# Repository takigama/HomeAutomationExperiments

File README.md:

# Experiments in Home Automation

So far, there is only the led strip here... there shall be more

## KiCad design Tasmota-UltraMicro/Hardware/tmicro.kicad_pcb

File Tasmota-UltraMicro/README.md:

# The Tasmota Ultra Micro

Like the Tasmota Micro, but smaller.

## Minimal.

I made it so I could put together some small sensor boards that plug straight into
a USB port. Unlike the original Tasmota Micro, this one has only a 'reg and direct
inputs to the GPIO's of the ESP8266 ESP01 board.

## Thanks...

Thanks to the tasmota guys for making the awesome firmware!

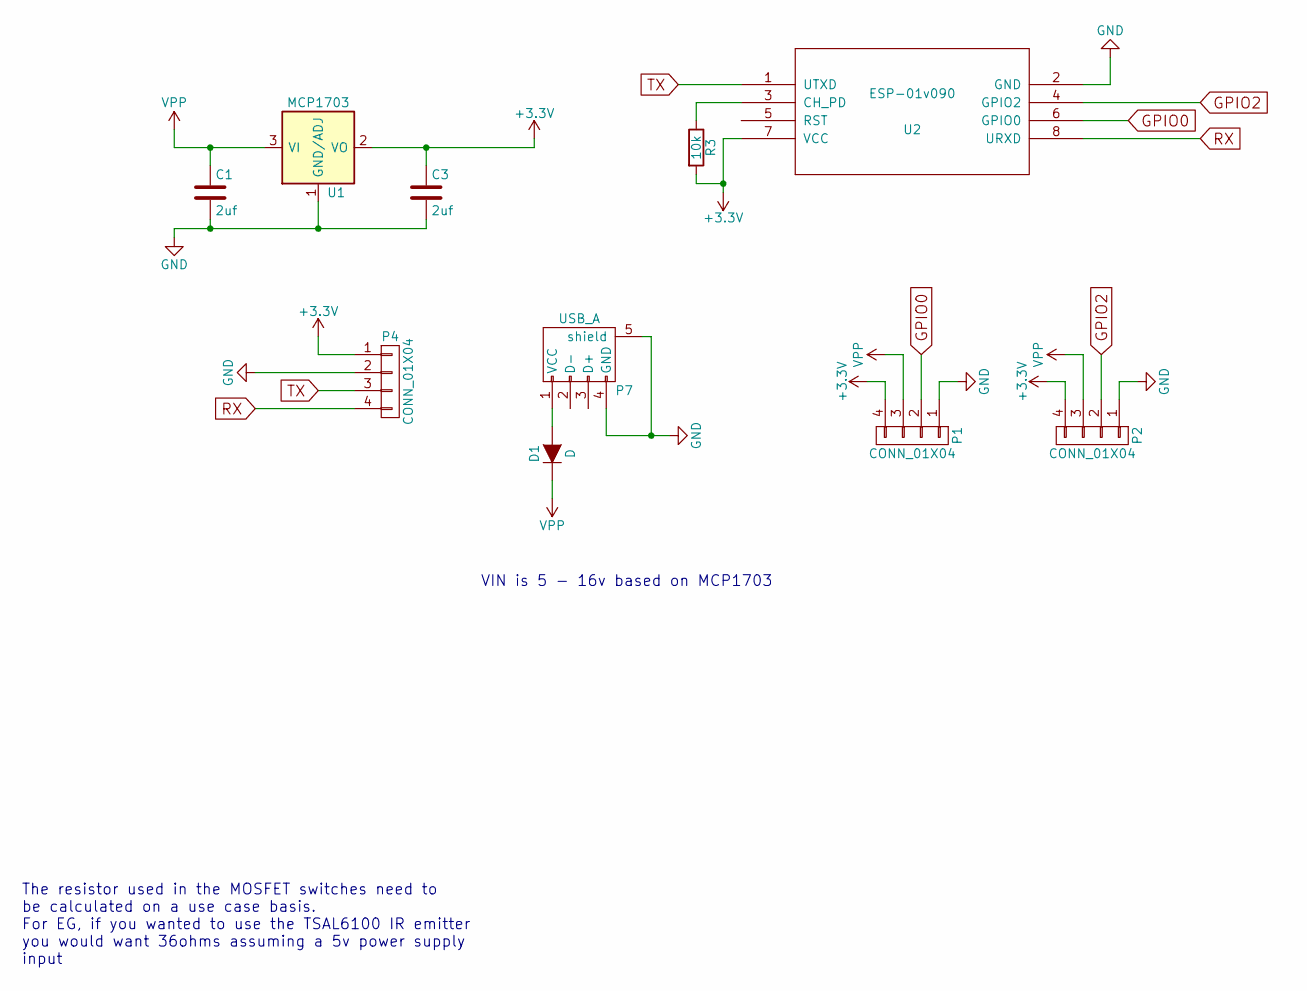
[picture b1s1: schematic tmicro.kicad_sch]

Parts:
C1, C3: 2uf; C_0805
D1: D; SMA_Standard
P1, P2, P4: CONN_01X04; PinHeader_1x04_P2.54mm_Vertical
P7: USB_A; USB_A_Multicomp_thruhole_oshpark
R3: 10k; R_0805
U1: MCP1703; SOT-23
U2: ESP-01v090; ESP-01

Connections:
+3V3: C3.1, P1.4, P2.4, P4.1, R3.2, U1.2 (VO), U2.7 (VCC)
GND: C1.2, C3.2, P1.1, P2.1, P4.2, P7.4 (GND), P7.5 (shield), U1.1 (GND/ADJ), U2.2 (GND)
GPIO0: P1.2, U2.6 (GPIO0)
GPIO2: P2.2, U2.4 (GPIO2)
unnamed: D1.2 (A), P7.1 (VCC)
unnamed: R3.1, U2.3 (CH_PD)
RX: P4.4, U2.8 (URXD)
TX: P4.3, U2.1 (UTXD)
VPP: C1.1, D1.1 (K), P1.3, P2.3, U1.3 (VI)

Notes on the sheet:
VIN is 5 - 16v based on MCP1703
The resistor used in the MOSFET switches need to be calculated on a use case basis. For EG, if you wanted to use the TSAL6100 IR emitter you would want 36ohms assuming a 5v power supply input

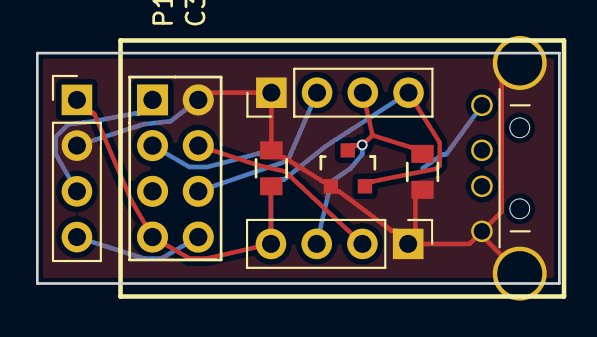
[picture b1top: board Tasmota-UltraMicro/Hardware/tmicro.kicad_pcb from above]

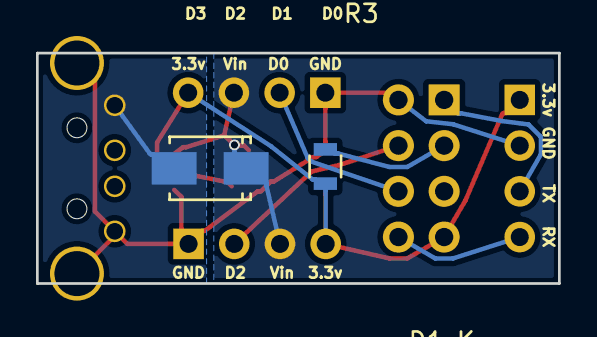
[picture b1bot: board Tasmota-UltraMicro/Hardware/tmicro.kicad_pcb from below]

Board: 2 copper layers, 29.0 x 12.8 mm, 10 parts (2 on the bottom side), 9 nets.

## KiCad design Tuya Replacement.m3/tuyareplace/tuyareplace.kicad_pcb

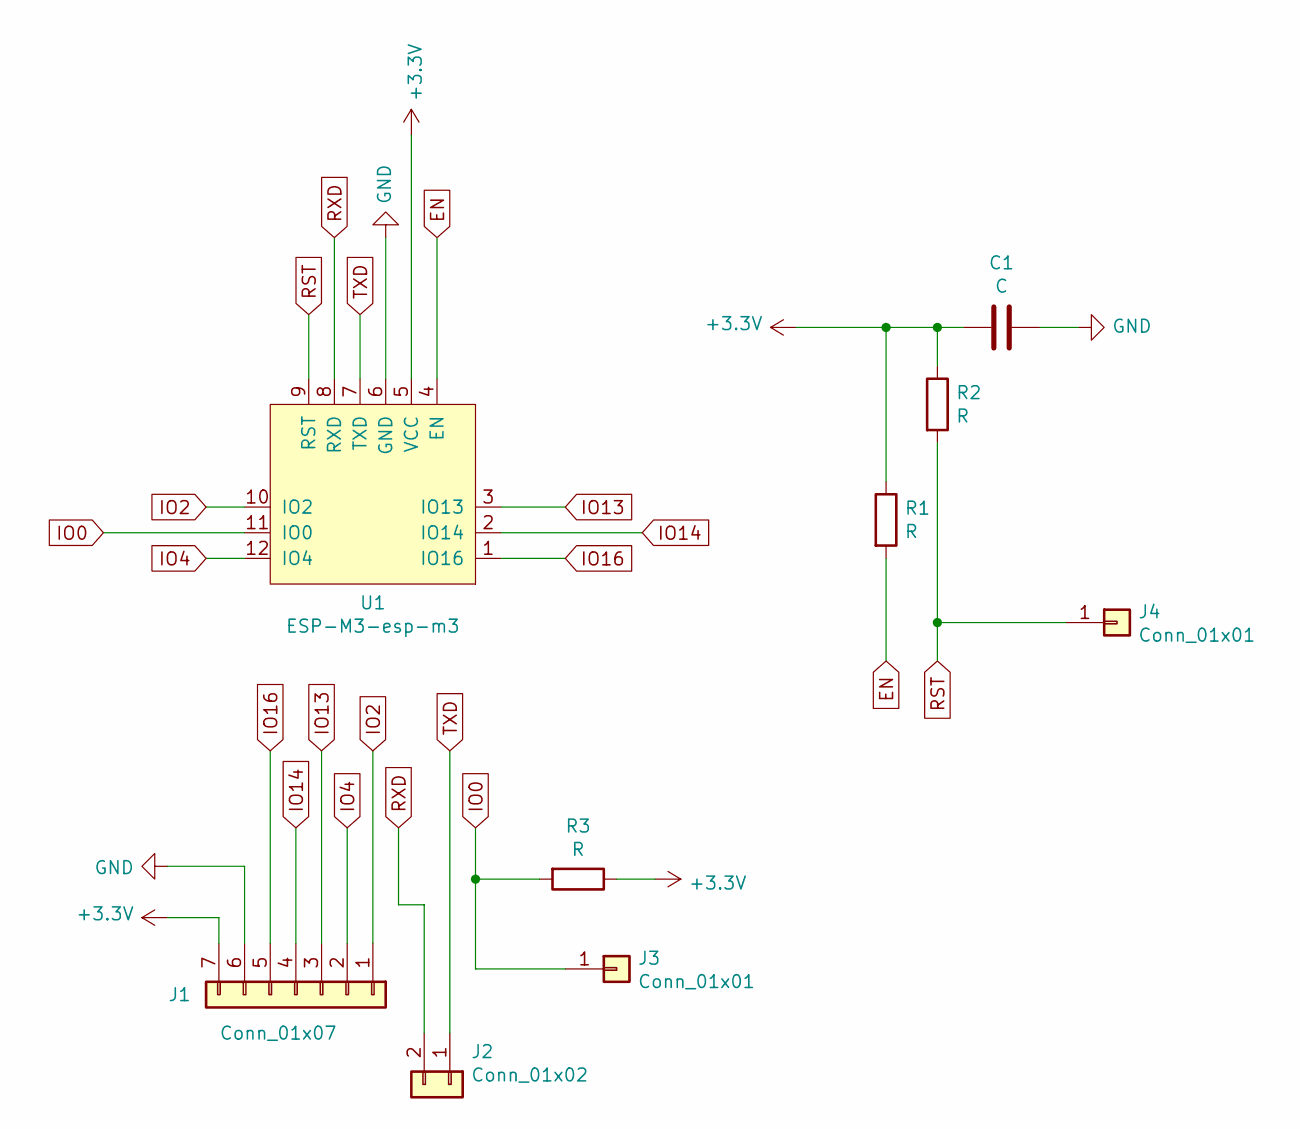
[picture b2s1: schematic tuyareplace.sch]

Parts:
C1: C; C_1206_3216Metric
J1: Conn_01x07; Tuya_TYWE2L_Edge
J2: Conn_01x02; PinHeader_1x02_P2.54mm_Vertical
J3, J4: Conn_01x01; PinHeader_1x01_P2.54mm_Vertical
R1, R2, R3: R; R_1206_3216Metric
U1: ESP-M3-esp-m3; ESP-M3

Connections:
+3V3: C1.2, J1.7, R1.1, R2.1, R3.1, U1.5 (VCC)
EN: R1.2, U1.4 (EN)
GND: C1.1, J1.6, U1.6 (GND)
IO0: J3.1, R3.2, U1.11 (IO0)
IO2: J1.1, U1.10 (IO2)
IO4: J1.2, U1.12 (IO4)
IO13: J1.3, U1.3 (IO13)
IO14: J1.4, U1.2 (IO14)
IO16: J1.5, U1.1 (IO16)
RST: J4.1, R2.2, U1.9 (RST)
RXD: J2.2, U1.8 (RXD)
TXD: J2.1, U1.7 (TXD)

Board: 2 copper layers, 9 parts (8 on the bottom side), 12 nets, no tracks yet.

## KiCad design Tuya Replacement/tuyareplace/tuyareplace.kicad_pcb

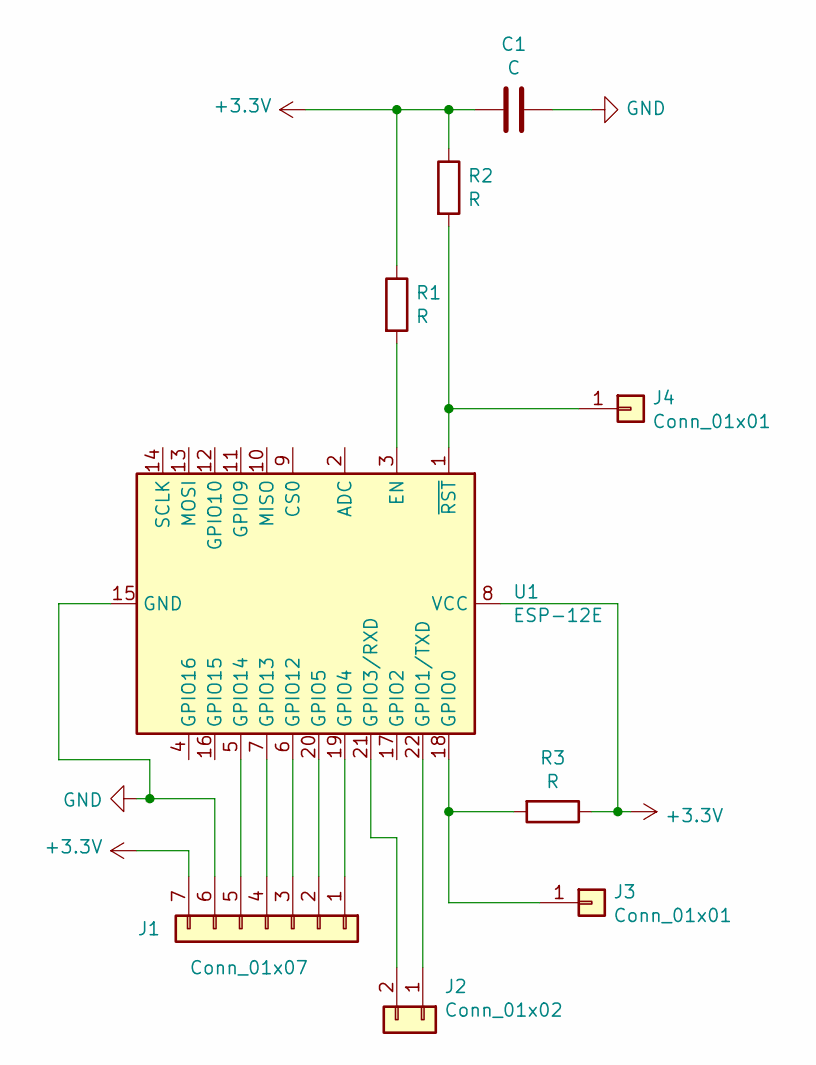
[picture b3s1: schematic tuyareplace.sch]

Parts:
C1: C; C_1206_3216Metric
J1: Conn_01x07; Tuya_TYWE2L_Edge
J2: Conn_01x02; PinHeader_1x02_P2.54mm_Vertical
J3, J4: Conn_01x01; PinHeader_1x01_P2.54mm_Vertical
R1, R2, R3: R; R_1206_3216Metric
U1: ESP-12E

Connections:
+3V3: C1.2, J1.7, R1.1, R2.1, R3.1, U1.8 (VCC)
GND: C1.1, J1.6, U1.15 (GND)
unnamed: J1.1, U1.19 (GPIO4)
unnamed: J1.2, U1.20 (GPIO5)
unnamed: J1.3, U1.6 (GPIO12)
unnamed: J1.4, U1.7 (GPIO13)
unnamed: J1.5, U1.5 (GPIO14)
unnamed: J2.1, U1.22 (GPIO1/TXD)
unnamed: J2.2, U1.21 (GPIO3/RXD)
unnamed: J3.1, R3.2, U1.18 (GPIO0)
unnamed: J4.1, R2.2, U1.1 (~RST)
unnamed: R1.2, U1.3 (EN)

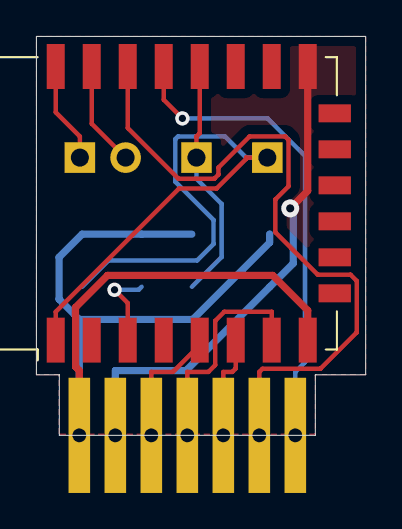
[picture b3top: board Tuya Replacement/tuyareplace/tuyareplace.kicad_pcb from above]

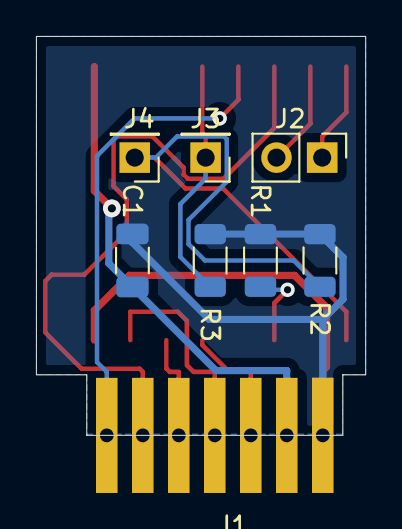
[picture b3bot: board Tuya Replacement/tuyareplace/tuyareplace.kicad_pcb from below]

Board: 2 copper layers, 18.3 x 22.2 mm, 9 parts (8 on the bottom side), 12 nets.

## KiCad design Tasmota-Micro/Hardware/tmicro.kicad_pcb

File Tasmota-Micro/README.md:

# The Tasmota Micro board

The tasmota micro (hope they dont mine me calling it that) is based off my
ledstrip controller with alot more flexibility build it. Its quite straight
forward but i'll make an image shortly of where the components go on the
board.

In short, the BOM is:

1. 2 x IRLML6244 (if needed - provides switching output for higher current
   loads) - Q1 and Q2
2. 2 x 2.2uf (or higher), one rated for 3.6v min and the othr rated at
   whatever input voltage you use. C3 - 3.3v, C1 Input voltage
3. 1 x diode (for stopping reverse polarity on the input) - D1
4. MCP1703-3.3 (3.3v regulator rated at 250ma - just enough for this) U1
5. 2 x resistors (you must size these yourself - but notes are provided) R1/2
6. 1 x 20k resistor - R3
7. 1 x MC32603 USB connector (only needed if you wish to poer the thing
   in the way i've show in my pictures, it can be just wired in.
8. Optionally a 2x4 header strip.
9. And of course, you will want an ESP-01S (with the larger flash, though I
   believe it can work ith the smaller 512k flash if you cut the firmware
   down a bit).

All resistors and caps are 0805 size. Diode is SMA.

## Putting it together

Personally, my first one was a hand solder job with a nothing-special type
of soldering iron and I found this to be quite easy (though I used a handheld
magnifying glass to get the components lined up). I put the first one together
with these tools just to make sure it could be done easily enough.

Generally I would normally use solder paste and a heatgun for the SMD
components, then hand solder in the connectors. Also note, in the images, i've
put JST connectors on there, this is just a serving suggestion, its not a
requirement and I wouldn't recommend it.

Also note, for the ESP module in the images, i've put on a 4x2 header so I
can easily remove the ESP-01 module - this isnt a requirement as it makes
the module quite a bit shorter if you choose not to do this. The ESP can still
be flashed if needed while soldered to the board, but you'll need some small
clips to do it.

## Connectors

### P2

Proves both raw input voltage or raw output voltage - i.e. you can push
power into the unit via one of these pins or provide power at the input
voltage as output (i.e. if your driving from USB these pins are 5v). Maximum
input voltate is 16v according to the MCP1703 tech specs, but I wouldn't
have a need to go beyond 12v myself.

### P3

These are the mosfet switched versions of GPIO2 and the RX line. They also
include current limiting resistors, R1 and R2 - you must size these
appropriaely for your project (or just bridge them and put resistors on
your actual device). Note, these pull to ground!

### P4

This header provides all 4 GPIO's as direct connections on the ESP at the
level of the ESP itself (3.3v), be aware though that depending on the state
of the ESP itself (which can draw about 170ma max - apparently), you can only
draw a maxmimum of about 80ma!.

### P5 

Output from the MCP1703 regulator is provided on these pins. This would
typically be 3.3v but if you've put in your own changes, what comes out
there is up to you, i.e. configure that in the tasmota gui.

### P6

Ground pins

## GPIO's

The device provides 4 GPIO's as well as two that can be switched via
mosfets.

So far i've tested the following components:

1. HC-SR505 movement sensor
2. BME280 - Temp/Pressure/Humidity
3. BMP180 - Temp/Pressure
4. BH1750 - Ambient light
5. CHQ1838 - IR Recv (runs at 3.3v, work well)
6. DS18B20 - Dallas Temp Sensor
7. TSAL6100 - IR Emitter (47ohm resistor on mosfet switch).
8. WS2812 - Addressable led strip.

So far they all work well - keen to try some more if and when i can think of
something.

## Current Limiting Resistors

On the "high current" switches (which are RX and GPIO2 on P3) you must either
provide some current limiting resistors or bridge the resistor tracks and put
the resistors on your device (assuming you need them at all). This also means
they must be sized to suit your needs (if putting them on the board). As an
example, I have one with a 47ohm resistor (to drive the TSAL6000 IR emitter)
and one with a 150ohm resistor (cause why not?).

Also note the mosfet i've put in the bom on this are rated for 6a, however I
wouldn't push my luck with it as the tracks can probably only withstand about
2A depending on the thickness of the solder traces and where you get them made.
Personally, I use OSH Park (note the connector the USB is designed with
circular holes for the USB mount ends - this is because OSH Park dont do oval
drill holes).

## More to come

As I get the opportunity i'll test some other devices to hang off it and will
definitely be continuing to update the board as time permits.

## Thanks...

Thanks to the tasmota guys for making the awesome firmware!

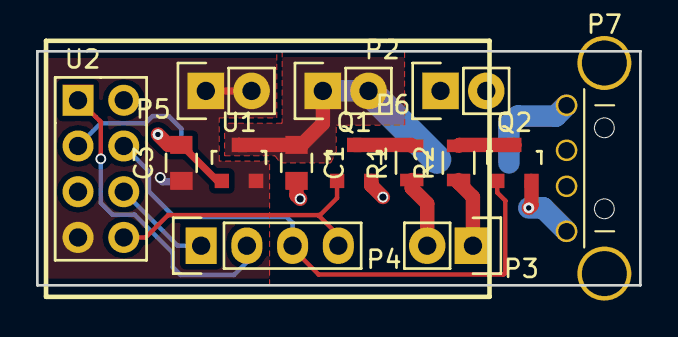
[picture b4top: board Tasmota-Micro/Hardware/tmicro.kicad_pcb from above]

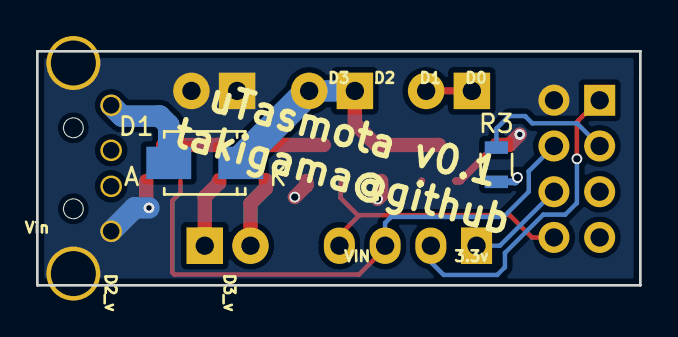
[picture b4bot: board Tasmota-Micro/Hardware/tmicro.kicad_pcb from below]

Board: 2 copper layers, 33.5 x 13.0 mm, 16 parts (2 on the bottom side), 13 nets.

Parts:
C1, C3: 2uf; C_0805
D1: D; SMA_Standard
P2, P3, P5, P6: CONN_01X02; Pin_Header_Straight_1x02
P4: CONN_01X04; Pin_Header_Straight_1x04
P7: USB_A; USB_A_Multicomp_thruhole_oshpark
Q1, Q2: IRLML6244; SOT-23
R1, R2: X; R_0805
R3: 10k; R_0805
U1: MCP1703; SOT-23
U2: ESP-01v090; ESP-01

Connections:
+3V3: C3.1, P5.1, P5.2, R3.2, U1.2, U2.7
GND: C1.2, C3.2, P6.1, P6.2, P7.4, P7.5, Q1.2, Q2.2, U1.1, U2.2
GPIO0: P4.1, U2.6
GPIO2: P4.3, Q2.1, U2.4
GPIO2_V: P3.1, R2.2
unnamed: D1.2, P7.1
unnamed: Q1.3, R1.1
unnamed: Q2.3, R2.1
unnamed: R3.1, U2.3
RX: P4.4, Q1.1, U2.8
RX_V: P3.2, R1.2
TX: P4.2, U2.1
VPP: C1.1, D1.1, P2.1, P2.2, U1.3

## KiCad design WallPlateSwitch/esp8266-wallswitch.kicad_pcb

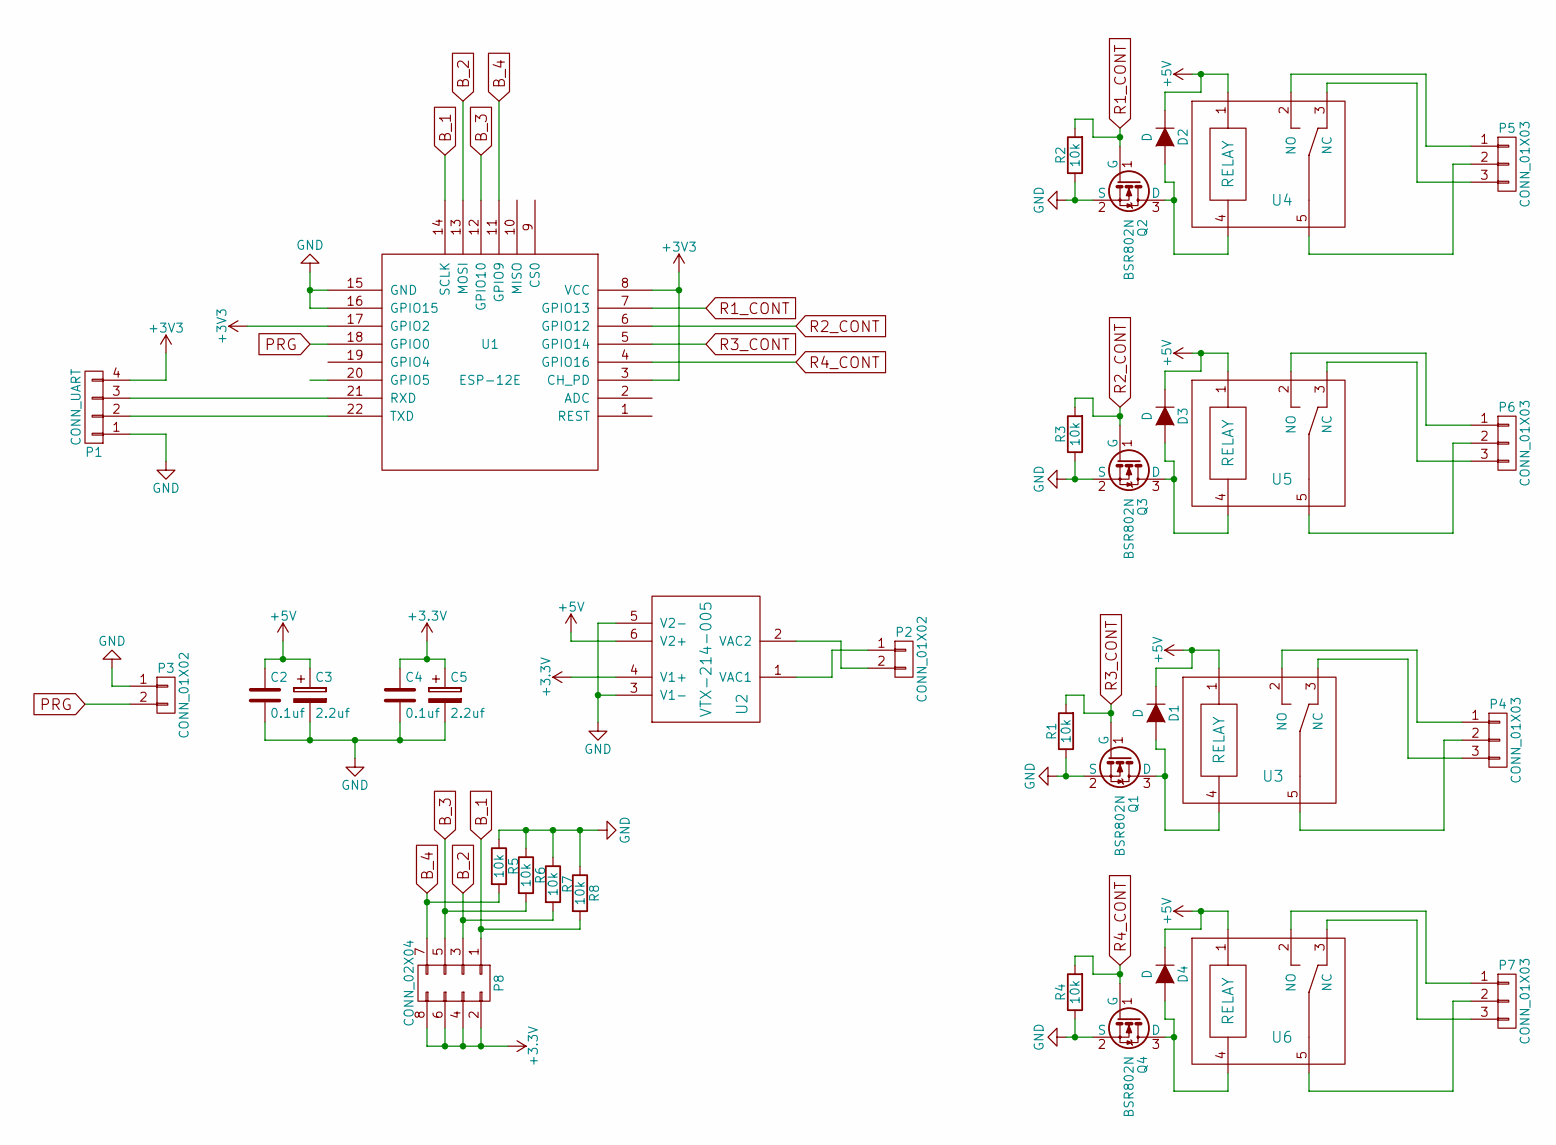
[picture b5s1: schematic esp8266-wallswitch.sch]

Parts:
C2, C4: 0.1uf; C_0805_HandSoldering
C3, C5: 2.2uf; SMD-1210_Pol
D1, D2, D3, D4: D; SMA_Standard
P1: CONN_UART; Pin_Header_Straight_1x04
P2: CONN_01X02; TerminalBlock_Pheonix_MKDS1.5-2pol
P3: CONN_01X02; Pin_Header_Straight_1x02
P4, P5, P6, P7: CONN_01X03; TerminalBlock_Pheonix_MKDS1.5-3pol
P8: CONN_02X04; Pin_Header_Straight_2x04
Q1, Q2, Q3, Q4: BSR802N; SOT-23_Handsoldering
R1, R2, R3, R4, R5, R6, R7, R8: 10k; R_0805_HandSoldering
U1: ESP-12E; ESP-12E-nohole
U2: VTX-214-005
U3, U4, U5, U6: RELAY; SONGLE_RELAY

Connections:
+5V: C2.1, C3.1, D1.1 (K), D2.1 (K), D3.1 (K), D4.1 (K), U2.6 (V2+), U3.1, U4.1, U5.1, U6.1
B_1: P8.1, R8.2, U1.14 (SCLK)
B_2: P8.3, R7.2, U1.13 (MOSI)
B_3: P8.5, R6.2, U1.12 (GPIO10)
B_4: P8.7, R5.2, U1.11 (GPIO9)
GND: C2.2, C3.2, C4.2, C5.2, P1.1, P3.1, Q1.2 (S), Q2.2 (S), Q3.2 (S), Q4.2 (S), R1.1, R2.1, R3.1, R4.1, R5.1, R6.1, R7.1, R8.1, U1.15 (GND), U1.16 (GPIO15), U2.3 (V1-), U2.5 (V2-)
unnamed: D1.2 (A), Q1.3 (D), U3.4
unnamed: D2.2 (A), Q2.3 (D), U4.4
unnamed: D3.2 (A), Q3.3 (D), U5.4
unnamed: D4.2 (A), Q4.3 (D), U6.4
unnamed: P1.2, U1.22 (TXD)
unnamed: P1.3, U1.21 (RXD)
unnamed: P2.1, U2.1 (VAC1)
unnamed: P2.2, U2.2 (VAC2)
unnamed: P4.1, U3.2 (NO)
unnamed: P4.2, U3.5
unnamed: P4.3, U3.3 (NC)
unnamed: P5.1, U4.2 (NO)
unnamed: P5.2, U4.5
unnamed: P5.3, U4.3 (NC)
unnamed: P6.1, U5.2 (NO)
unnamed: P6.2, U5.5
unnamed: P6.3, U5.3 (NC)
unnamed: P7.1, U6.2 (NO)
unnamed: P7.2, U6.5
unnamed: P7.3, U6.3 (NC)
PRG: P3.2, U1.18 (GPIO0)
R1_CONT: Q2.1 (G), R2.2, U1.7 (GPIO13)
R2_CONT: Q3.1 (G), R3.2, U1.6 (GPIO12)
R3_CONT: Q1.1 (G), R1.2, U1.5 (GPIO14)
R4_CONT: Q4.1 (G), R4.2, U1.4 (GPIO16)

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
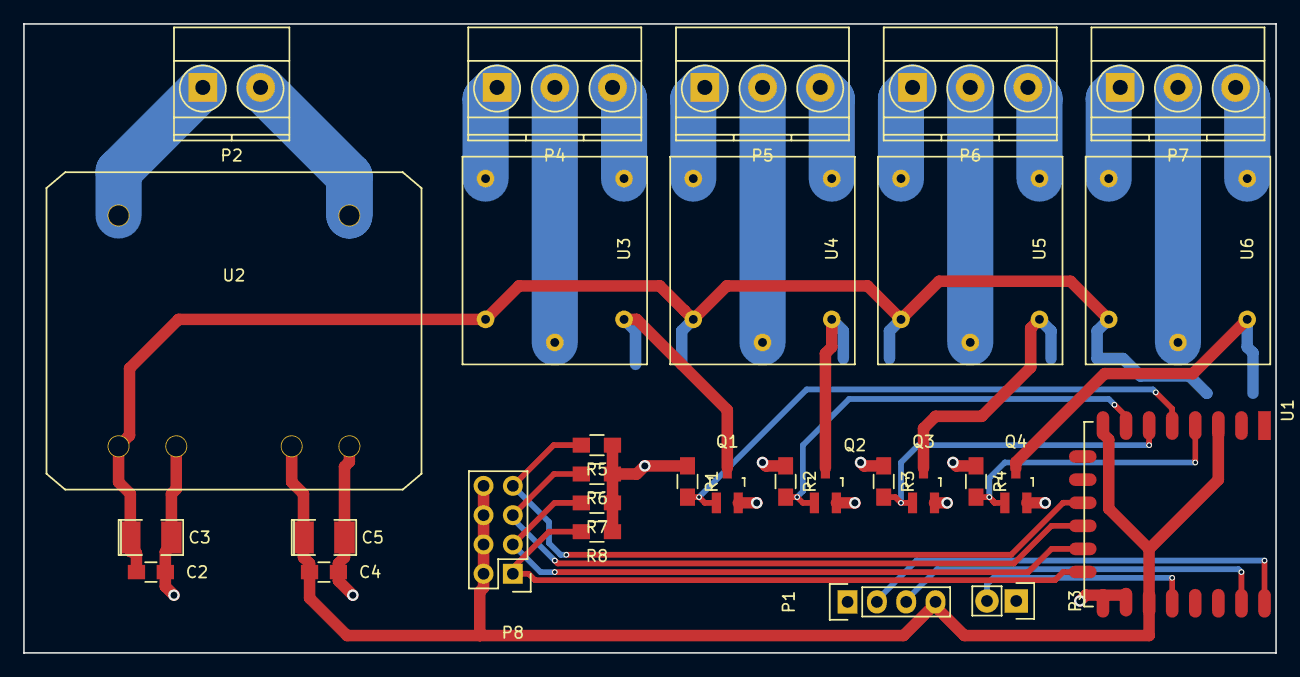
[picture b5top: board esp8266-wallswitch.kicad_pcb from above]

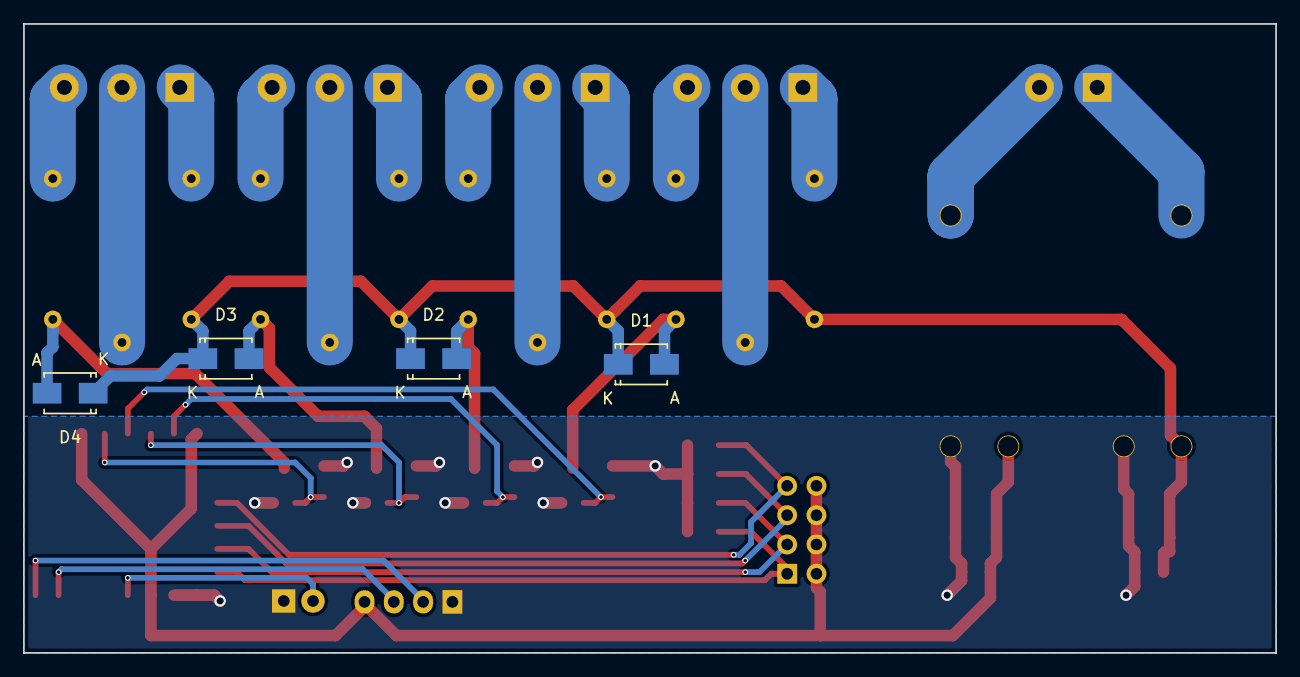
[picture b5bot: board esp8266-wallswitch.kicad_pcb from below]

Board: 2 copper layers, 108.5 x 54.5 mm, 34 parts (4 on the bottom side), 32 nets.

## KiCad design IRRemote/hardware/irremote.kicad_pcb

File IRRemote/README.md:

# ESP8266 based IR remote

This project is an ESP8266/homie based IR remote receiver/transmitter
The board uses a ESP12E as its base. There are several parts that can
be left off if not needed. For EG, it uses 4 transistors, one for each
of 4 IR leds, each can handle about 500ma of output at 5v, which means
all 4 together give about 2a across 4 connectors so size appropriately

The board has a connections for a TEMT6000 Light sensor as well as the
DS18B20 single wire temperature chip. All the spare GPIO's are exposed
as well as the SPI interface to be used for whatever you like. The ADC
pin of the ESP is connected to the light sensor, so if you want to use
it for a different purpose, you can connect it there.

## Homie + ESP8266

This board was designed with homie in mind and uses MQTT to comm's
with its controller. In my case, Home Assistant. As this hasnt been
written yet, i'll get back to you shortly!

## Image

## Warning!

Only just got the board back from OSHPark, but so far it works ok. I've
managed to control a device via IR after learning its IR message via
the ESP8266 IR library. Fairly happy so far. Temperature is also working
quite well. Only issue i have with it is that the SMD push button 
footprint I used is slightly smaller then the actual PB's I have, which
made soldering them on quite the pain.

## Changes

* moved to a microusb connector for power
* flipped the IR receiver so its pointing outward
* fixed the push buttons for the correct SMD push button

OshPark Project: [Link](https://oshpark.com/shared_projects/F54xaFnq)

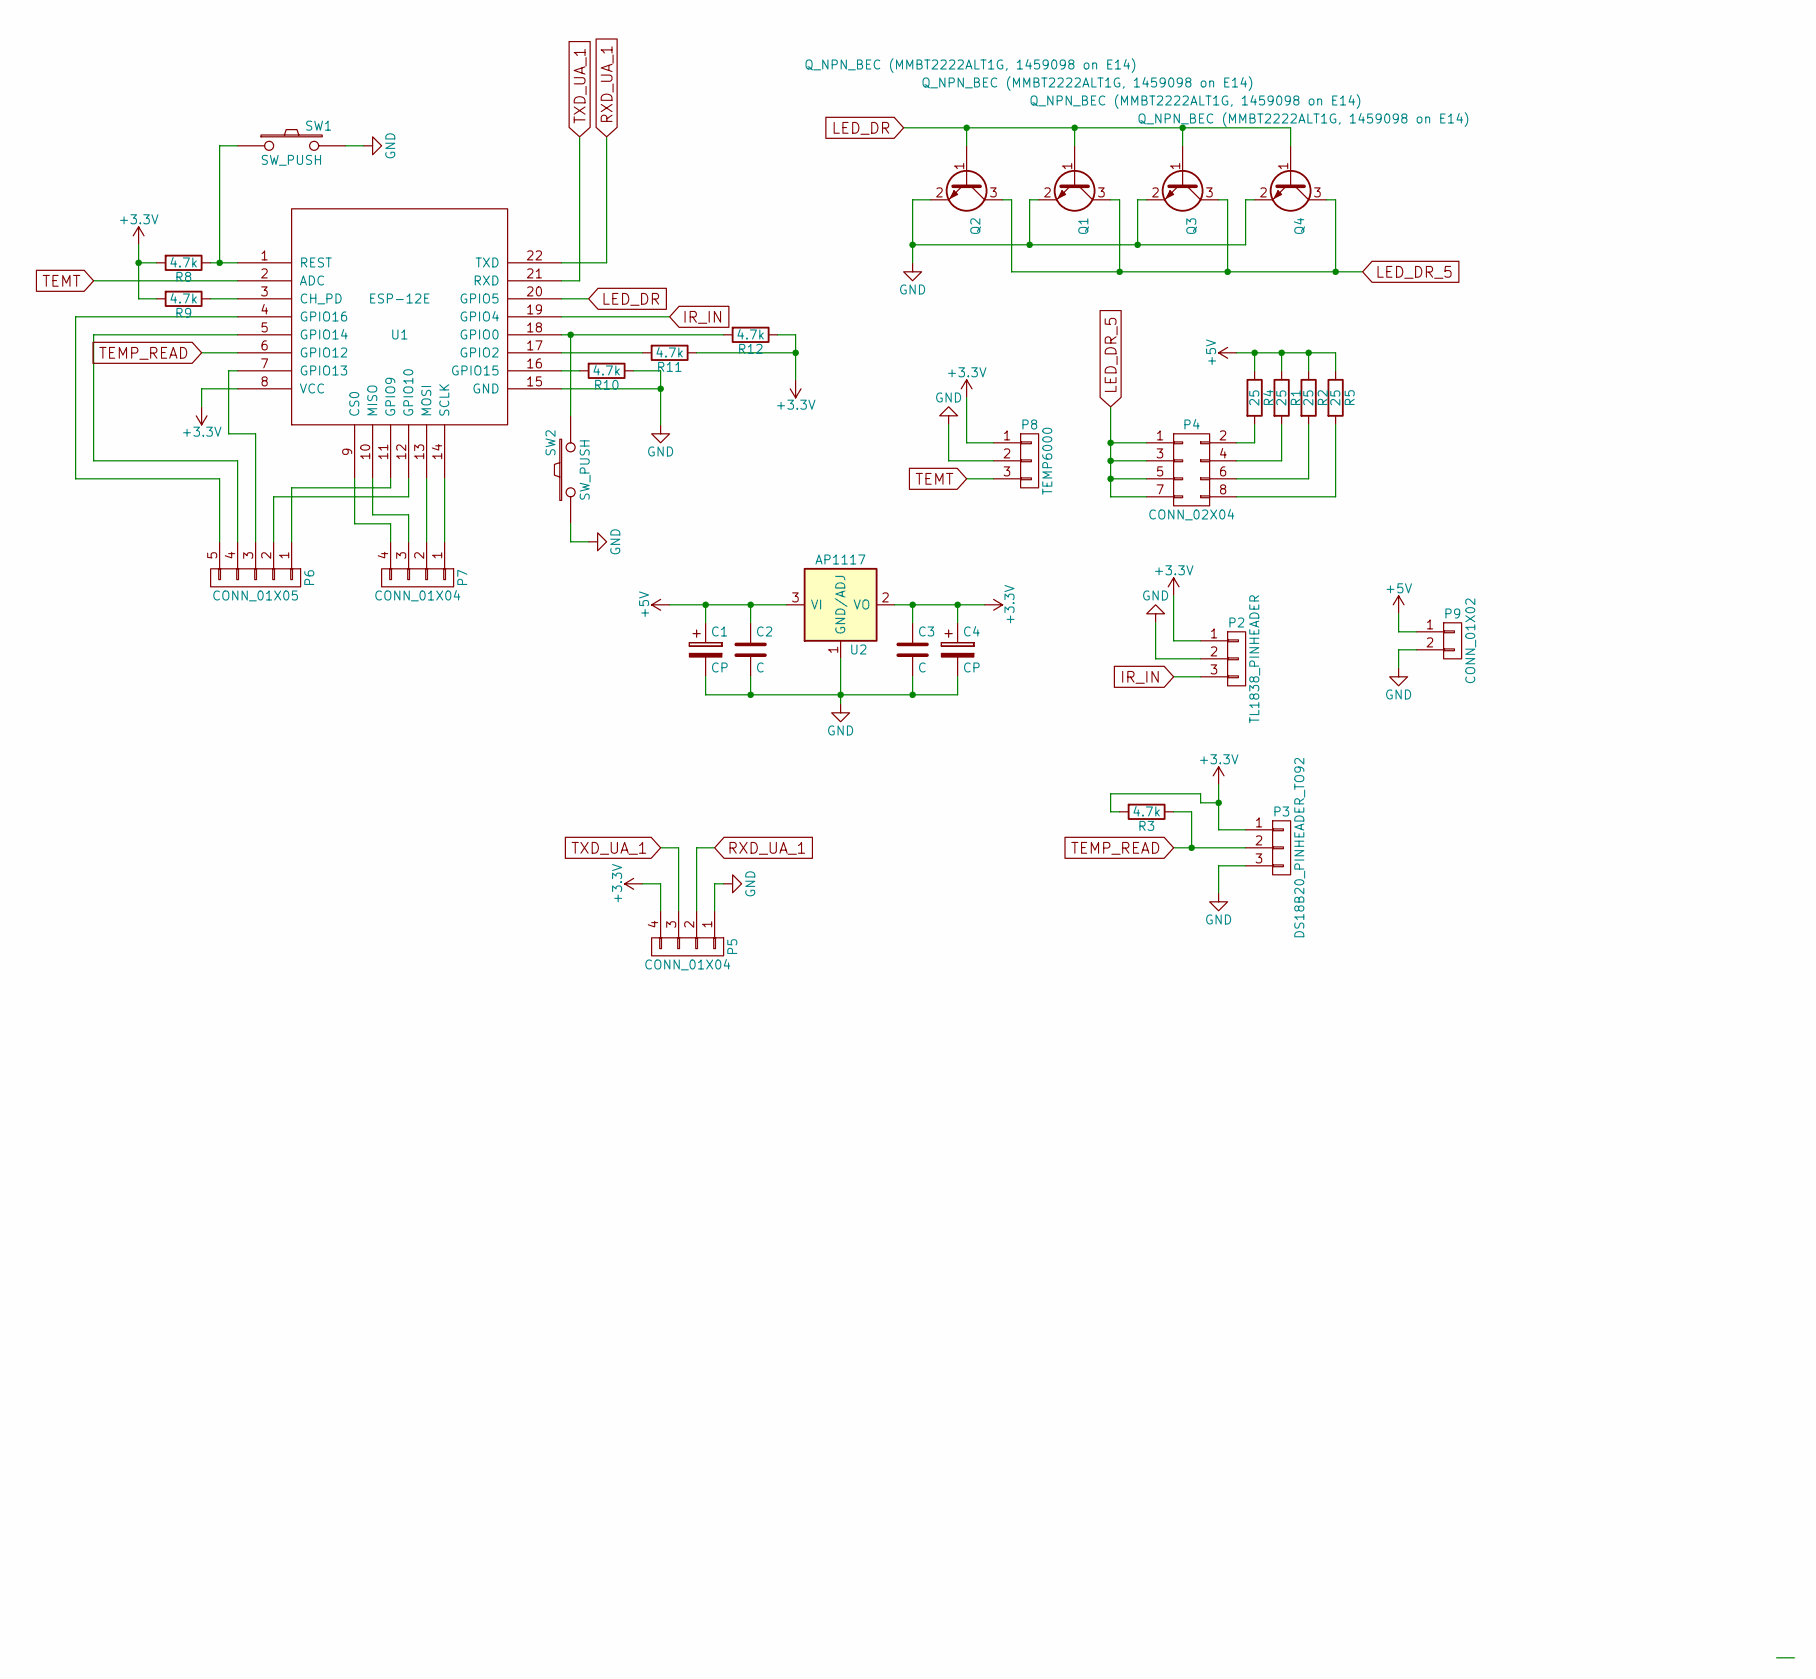
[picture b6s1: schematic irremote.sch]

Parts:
C1, C4: CP; TantalC_SizeB_EIA-3528_Reflow
C2, C3: C; C_0805
P2: TL1838_PINHEADER; Pin_Header_Straight_1x03
P3: DS18B20_PINHEADER_TO92; TO-92_Inline_Narrow_Oval
P4: CONN_02X04; Pin_Header_Straight_2x04
P5, P7: CONN_01X04; Pin_Header_Straight_1x04
P6: CONN_01X05; Pin_Header_Straight_1x05
P8: TEMP6000; Pin_Header_Straight_1x03
P9: CONN_01X02; Pin_Header_Straight_1x02
Q1, Q2, Q3, Q4: Q_NPN_BEC (MMBT2222ALT1G, 1459098 on E14); SOT-23
R1, R2, R4, R5: 25; R_0805_HandSoldering
R3, R8, R9, R10, R11, R12: 4.7k; R_0805_HandSoldering
SW1, SW2: SW_PUSH; SW_SPST_FSMSM
U1: ESP-12E
U2: AP1117; SOT-23_Handsoldering

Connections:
+3V3: C3.1, C4.1, P2.1, P3.1, P5.4, P8.1, R3.2, R8.2, R9.2, R11.1, R12.1, U1.8 (VCC), U2.2 (VO)
+5V: C1.1, C2.1, P9.1, R1.1, R2.1, R4.1, R5.1, U2.3 (VI); also elsewhere on the board
GND: C1.2, C2.2, C3.2, C4.2, P2.2, P3.3, P5.1, P8.2, P9.2, Q1.2 (E), Q2.2 (E), Q3.2 (E), Q4.2 (E), R10.1, SW1.2, SW2.1, U1.15 (GND), U2.1 (GND/ADJ); also elsewhere on the board
IR_IN: P2.3, U1.19 (GPIO4)
LED_DR: Q1.1 (B), Q2.1 (B), Q3.1 (B), Q4.1 (B), U1.20 (GPIO5)
LED_DR_5: P4.1, P4.3, P4.5, P4.7, Q1.3 (C), Q2.3 (C), Q3.3 (C), Q4.3 (C)
unnamed: P4.2, R4.2
unnamed: P4.4, R1.2
unnamed: P4.6, R2.2
unnamed: P4.8, R5.2
unnamed: P6.1, U1.11 (GPIO9)
unnamed: P6.2, U1.12 (GPIO10)
unnamed: P6.3, U1.7 (GPIO13)
unnamed: P6.4, U1.5 (GPIO14)
unnamed: P6.5, U1.4 (GPIO16)
unnamed: P7.1, U1.14 (SCLK)
unnamed: P7.2, U1.13 (MOSI)
unnamed: P7.3, U1.10 (MISO)
unnamed: P7.4, U1.9 (CS0)
unnamed: R8.1, SW1.1, U1.1 (REST)
unnamed: R9.1, U1.3 (CH_PD)
unnamed: R10.2, U1.16 (GPIO15)
unnamed: R11.2, U1.17 (GPIO2)
unnamed: R12.2, SW2.2, U1.18 (GPIO0)
RXD_UA_1: P5.2, U1.22 (TXD)
TEMP_READ: P3.2, R3.1, U1.6 (GPIO12)
TEMT: P8.3, U1.2 (ADC)
TXD_UA_1: P5.3, U1.21 (RXD)

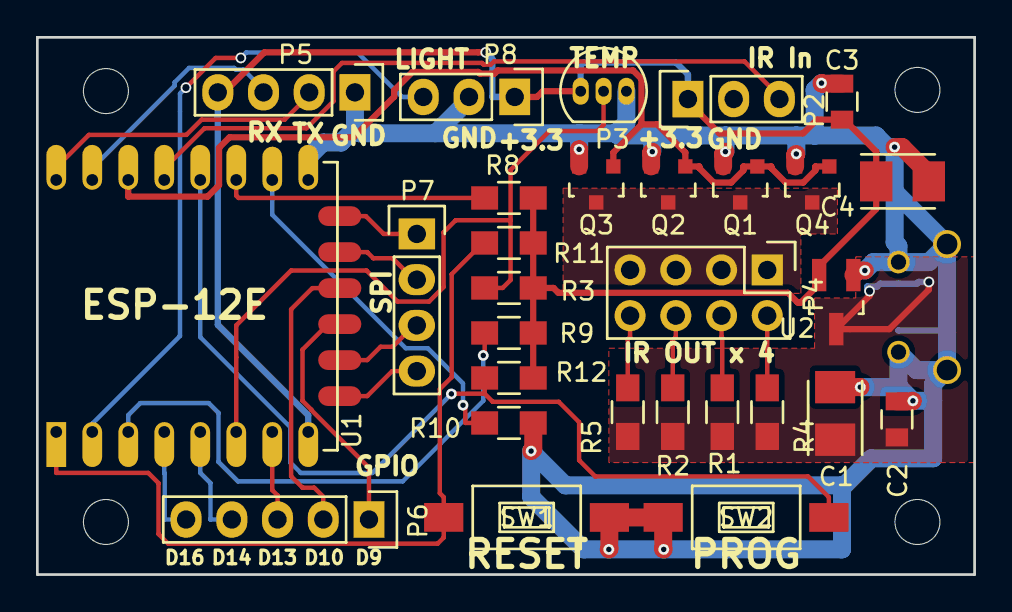
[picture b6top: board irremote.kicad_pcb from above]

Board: 2 copper layers, 52.1 x 29.8 mm, 34 parts (1 on the bottom side), 28 nets.

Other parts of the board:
P1: USB_OTG; USB_Micro-B-OshPark
REF01, REF02, REF03, REF04: MountingHole_2-5mm

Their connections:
+5V: P1.1; also elsewhere on the board
GND: P1.5, P1.6; also elsewhere on the board

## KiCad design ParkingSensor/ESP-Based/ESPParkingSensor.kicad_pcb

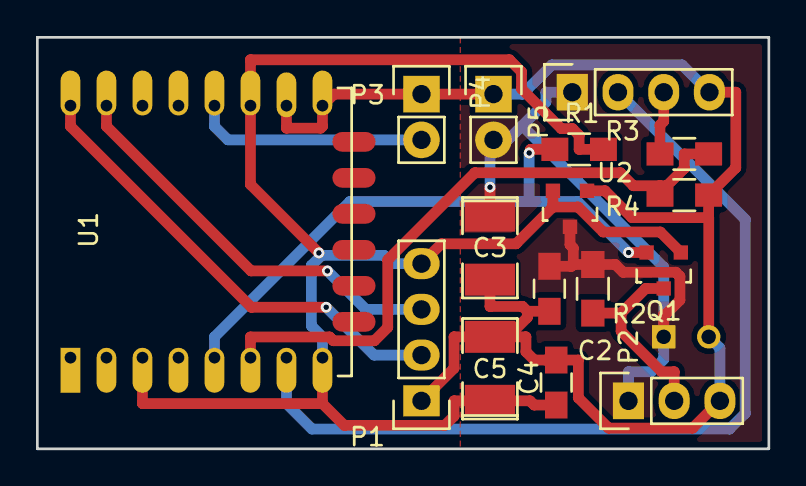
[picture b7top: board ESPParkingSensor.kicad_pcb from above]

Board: 2 copper layers, 40.6 x 22.9 mm, 17 parts (1 on the bottom side), 11 nets.

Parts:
C1: 1000uf; C_Radial_D6.3_L11.2_P2.5
C2, C4: 0.1uf; C_0805_HandSoldering
C3, C5: 2.2uf; SMD-1210_Pol
P1: CONN_UART; Pin_Header_Straight_1x04
P2: CONN_WS2812; Pin_Header_Straight_1x03
P3, P5: CONN_01X02; Pin_Header_Straight_1x02
P4: CONN_US; Pin_Header_Straight_1x04
Q1: BSS138; SOT-23
R1, R2: 10k; R_0805_HandSoldering
R3: 1.7k; R_0805_HandSoldering
R4: 3.3k; R_0805_HandSoldering
U1: ESP-12E
U2: MCP1700; SOT-23

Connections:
+3V3: C4.1, C5.1, P1.4, Q1.1, R1.1, U1.3, U1.8, U1.17, U2.2
+5V: C1.1, C2.1, C3.1, P2.1, P4.1, P5.2, R2.1, U2.3
BB_LINE: Q1.2, R1.2, U1.5
BB_LINE_5: P2.2, Q1.3, R2.2
ECHO: P4.3, R3.1
GND: C1.2, C2.2, C3.2, C4.2, C5.2, P1.1, P2.3, P3.1, P4.4, P5.1, R4.2, U1.15, U1.16, U2.1
unnamed: P1.2, U1.22
unnamed: P1.3, U1.21
unnamed: R3.2, R4.1, U1.6
PRG: P3.2, U1.18
TRG: P4.2, U1.7

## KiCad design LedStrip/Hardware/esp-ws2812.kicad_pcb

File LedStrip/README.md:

# Dont build this....

Im currently in the process of re-designing this board based on the tasmota
firmware so I would hold off building one of these boards in favour of my new
uTasmota board - very similar size, and more flexible.

If you really do want to build this board, go ahead, but rather than using
my own homie-based firmware, flash the tasmota firmware (make sure you using
a board that has 1mb of flash, not 512k).

.... continueing on...

# Led strip for ESP8266 with homie and hardware

This is a little code base and a hardware board designed to work with homie
and the WS2812 led strips. The hardware component is based on the ESP-01, that
is you print the board, put its components on, then add an ESP-01 (or s).

* [OSHPark Project](https://oshpark.com/shared_projects/sWWzDNyt)
* [Small Demo Video](https://www.youtube.com/watch?v=C1is4zkPhkE)
* [Pointer and Fire Modes](https://www.youtube.com/watch?v=obZJblPsRek)
* [Putting it together video](https://youtu.be/5BQnyncV6P0)

Technically, the board could be used to drive anything if all you need is 5v
input, 1x5v GPIO and 3 x 3.3v GPIO (TX/RX can be used for multiple things, 
including I2C or just straight GPIO). Note though that GPIO2 drives the 5v
output and care must be taken because pulling GPIO2 low on boot, causes it to
boot in a different mode!

## The Board:

## Messages
- devices/#DEVICE_ID/switch/switch/set - changes on/off
- devices/#DEVICE_ID/switch/status - reports status here
- devices/#DEVICE_ID/brightness/brightness/set - change brightness (0-255)
- devices/#DEVICE_ID/color/color/set - changes the colour state (R,G,B)
- devices/#DEVICE_ID/color/color - colour report

Can be used with ranges, i.e. sending 0,20,on to switch will only turn on
leds 0 to 20 - isnt required

## Home Assistant config
looks very roughly like this (its a moving target):
```
light:
  - platform: mqtt
    name: "esplight"
    command_topic: "devices/dev1/switch/switch/set"
    rgb_command_topic: "devices/dev1/led/color/set"
    rgb_value_template: "value.rgb|join(',')"
    brightness_state_topic: "devices/dev1/brightness/brightness/set"
    brightness_command_topic: "devices/dev1/brightness/brightness/set"
    qos: 0
    payload_on: "on"
    payload_off: "off"
    optimistic: false
    state_topic: "devices/dev1/switch/status"

```

## work in progres
Note, i just started this in late october - its very much a work in progress!

## TODO's

### DONE
1. Moved to fastled lib (not really liking it much) - DONE
2. change messages to allow for sub-ranges - DONE
3. add some fixed effects (fire, pointer, tv)

### Not Done
4. make number of leds dynamic (and saved in eeprom) - trickier than i'd hoped

## Hardware
The kicad project is just a little daughter board for an ESP-01 that makes
it easier to control ws2812's. 5V input with a reg on board and a level
shifter for the signal line - see the bom file (html format) for the components
to get on the board. Its much easier to make than it looks, dont let SMD
scare you!

### Alternative Parts

The board uses an MCP1700 Reg to create the 3.3v needed by the board. This can
be replaced with a different REG to support higher input voltages (6v with the
MCP1700), but can be something like an [MCP1703T](http://www.farnell.com/datasheets/1268705.pdf?_ga=1.231719964.246887079.1486429056)
which can handle up to 16v (for 12v led strips?)

In the built board, i've used a 100uf 6v CAP (as per recommendations, but anything
that fits is suitable, there are 0.1F 5.5v caps that are quite small and would also
fit on board.

Parts from the bom:
* BSS138 (SOT-23 package)
* 2-10uf 6v+ Tant x 2 (1210 package)
* 0.1-2uf 6v+ Ceramic x 2 (0805 package)
* MCP1700 3.3v LDO Reg (SOT-23 package)
* 10k resistor x 2 (0805 package)
* ESP-01 x 1
* Bunch of pin headers

You can also either provide female pin headers for the ESP-01 or
just solder it direct to the board (more compact permanently soldered)

## Pin Layout

;

## Attributions
Level shifter is a reproduction of sparkfun's bi-directional level shifter, as
available here:

[SparkFun Logic Level Converter](https://www.sparkfun.com/products/12009)

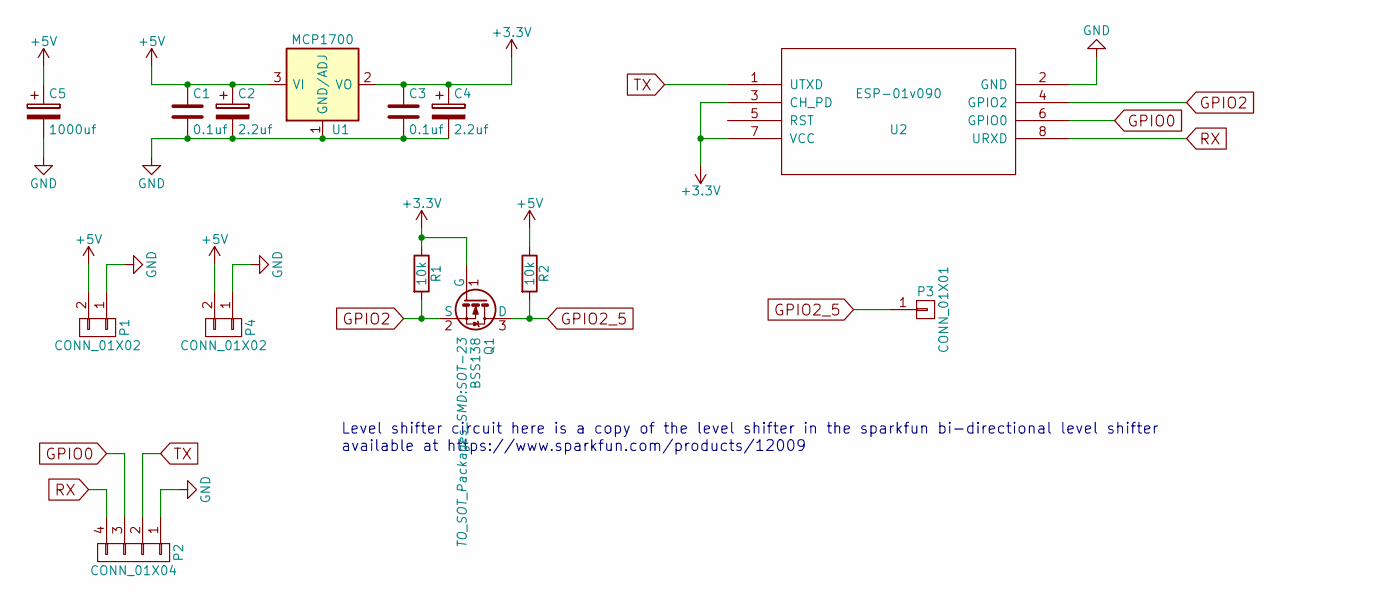
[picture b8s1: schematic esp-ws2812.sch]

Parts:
C1, C3: 0.1uf; C_0805_HandSoldering
C2, C4: 2.2uf; TantalC_SizeB_EIA-3528_Wave
C5: 1000uf; C_Radial_D6.3_L11.2_P2.5
P1, P4: CONN_01X02; Pin_Header_Straight_1x02
P2: CONN_01X04; Pin_Header_Straight_1x04
P3: CONN_01X01; Pin_Header_Straight_1x01
Q1: BSS138; SOT-23
R1, R2: 10k; R_0805_HandSoldering
U1: MCP1700; SOT-23
U2: ESP-01v090; ESP-01

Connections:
+3V3: C3.1, C4.1, Q1.1 (G), R1.1, U1.2 (VO), U2.3 (CH_PD), U2.7 (VCC)
+5V: C1.1, C2.1, C5.1, P1.2, P4.2, R2.1, U1.3 (VI)
GND: C1.2, C2.2, C3.2, C4.2, C5.2, P1.1, P2.1, P4.1, U1.1 (GND/ADJ), U2.2 (GND)
GPIO0: P2.3, U2.6 (GPIO0)
GPIO2: Q1.2 (S), R1.2, U2.4 (GPIO2)
GPIO2_5: P3.1, Q1.3 (D), R2.2
RX: P2.4, U2.8 (URXD)
TX: P2.2, U2.1 (UTXD)

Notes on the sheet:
Level shifter circuit here is a copy of the level shifter in the sparkfun bi-directional level shifter available at https://www.sparkfun.com/products/12009

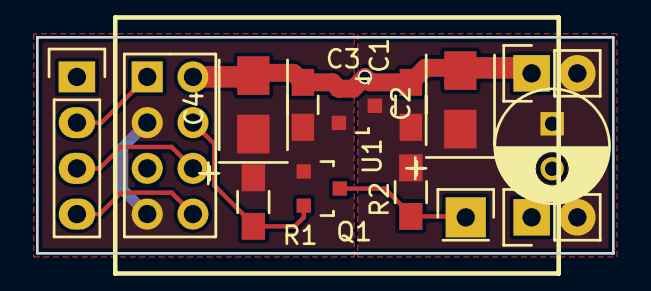
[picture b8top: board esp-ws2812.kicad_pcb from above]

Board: 2 copper layers, 32.0 x 12.0 mm, 14 parts (0 on the bottom side), 8 nets.
